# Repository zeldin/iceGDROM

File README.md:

iceGDROM
========

This is an implementation of IDE and the "Sega Packet Interface"
as used by the Dreamcast GD-ROM drive, using an iCE40 FPGA.

In addition to the IDE interface itself, and the accompanying CD-DA
interface, the FPGA bitstream implements an RV32EMC-compatible CPU and
an SD Card interface.  Software running on the CPU responds to
disc access commands from the Dreamcast by fetching data from disc
images on an SD Card.

For more detailed information, please see [the webpage][1].

This is free software (and hardware) licensed under the GNU
General Public License version 3.

Hardware
--------

The hardware is based on the Lattice iCE40-HX8K Breakout Board.
In order to connect this board to the Dreamcast motherboard, a
custom "riser board" with the appropriate connectors and some
additional components is used.  The design files for this can be
found in the `pcb/riser` directory.  The bill of materials can be
found in the file `pcb/riser/bom.txt`.  The pin headers with a `J`
designation should be soldered to the Breakout Board (pins facing downwards).

The components CN4, R8, D1, and JP2 through JP4 are optional.  They
are a passthrough for a slave hard drive, and not used by the GD-ROM
emulator.

For the hardware to be complete, the following additional things are
needed:

* A USB-mini cable to connect CN6 to the Breakout Board.  This is how
  the Breakout Board is powered when not attached to a host computer.
* An SD Card module, to connect to CN5.
* Rubber feet or similar to support the weight of the board in the
  corners not resting on CN1.

Required tools
--------------

To build the FPGA bitstream, the following tools are needed:

* Yosys 0.6
* arachne-pnr
* icestorm

To build the RISC-V software, the following tools are needed:

* riscv32-unknown-elf gcc 10.2.0
* riscv32-unknown-elf binutils 2.34.0

Building
--------

Building is done by running GNU make.  Running make at the top level
will build everything, running it in a subdir will build that part.
Note that building in fpga requires the rv32 stuff to be built first.

The file `rv32/source/config.h` can be modified to adapt to the polarity
of the CD signal on the chosen SD Card module, or to enable debug traces
on the serial port of the FTDI chip.

In order to flash the FPGA bitstream to the breakout board, run
`make flash`.

Making image files
------------------

Building the project will also create a host tool in `tools/obj/makegdimg`
which can create image files from either `.gdi` files (for GD-ROM images)
or from `.nrg` or `.cdi` files (for MIL-CD and audio CD images).  The
image files should be named `DISC0000.GI0`, `DISC0001.GI0` etc on the
SD Card.  To switch between images, extract and reinsert the SD Card.

Acknowledgements
----------------

* RISC-V softcore "VexRiscv" was developed by Charles Papon
* GD-ROM connector pinout was provided by OzOnE
* SD Card and FAT code based on sdfatlib by Bill Greiman
* DiscJuggler reader code based on CDIrip by DeXT/Lawrence Williams

[1]: http://mc.pp.se/dc/gdromemu.html

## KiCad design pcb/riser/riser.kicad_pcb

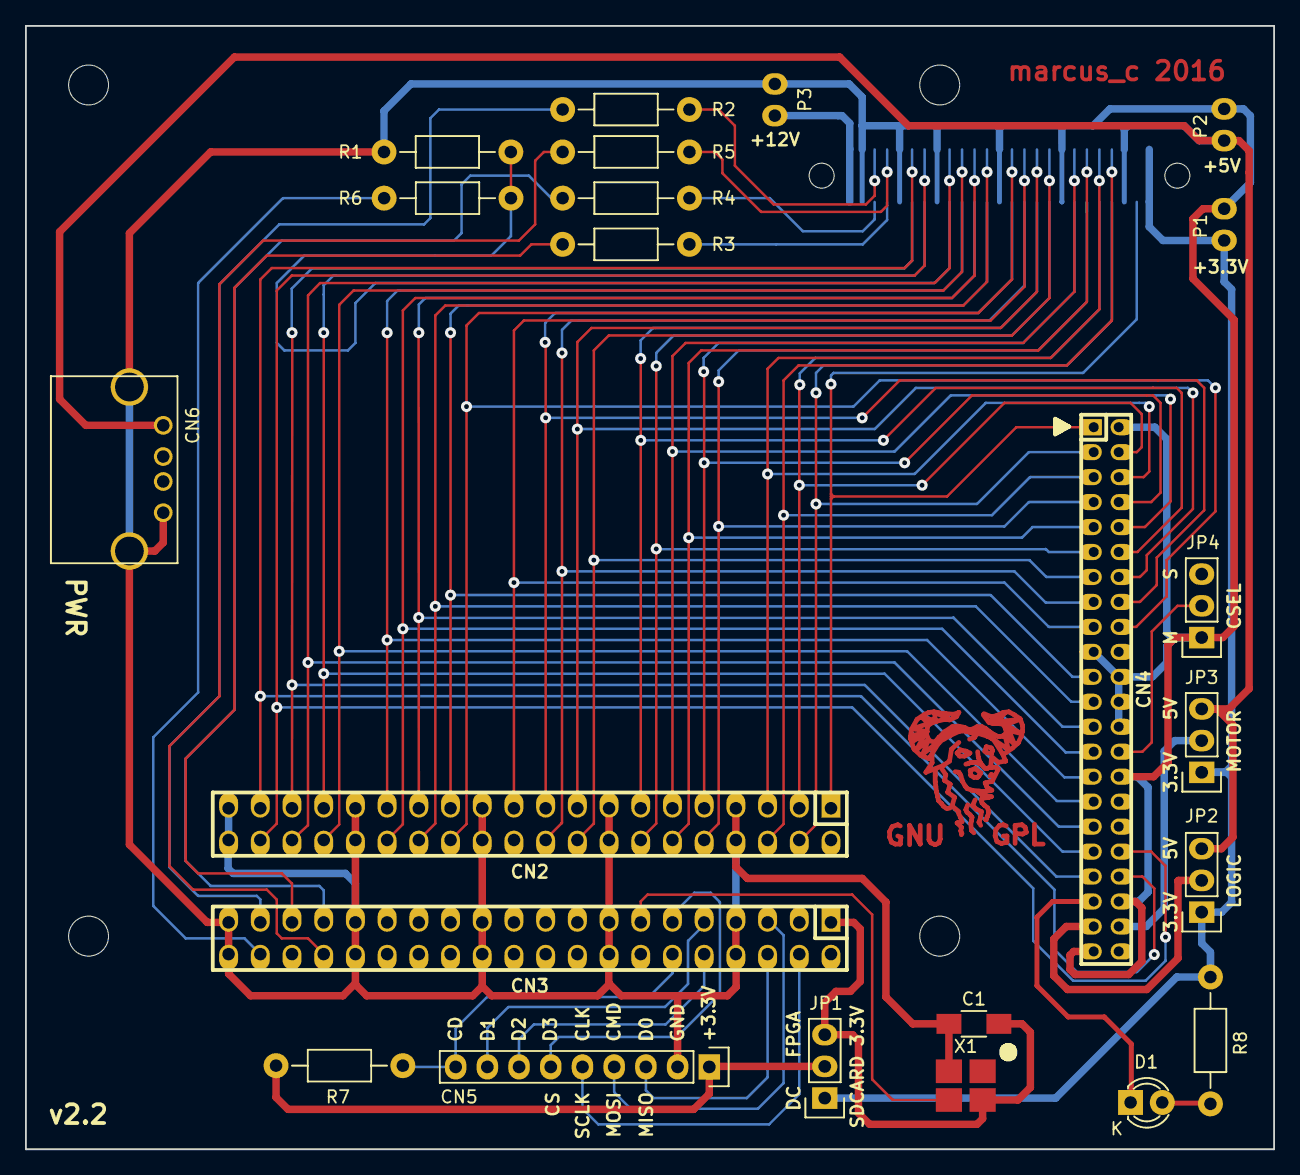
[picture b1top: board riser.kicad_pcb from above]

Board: 2 copper layers, 100.0 x 90.0 mm, 24 parts (1 on the bottom side), 57 nets.

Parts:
C1: 0.01u; C_1206_HandSoldering
CN1: Molex_52602_0579
CN2, CN3: CONN_02X20; pin_socket_20x2
CN4: CONN_02X22; pin_strip_2mm_22x2
CN5: CONN_01X09; Pin_Header_Straight_1x09
CN6: USB-A; USB_A
D1: LED; LED-3MM
JP1, JP2, JP3, JP4: JUMPER3; Pin_Header_Straight_1x03
P1, P2, P3: CONN_01X02; WireConnection_1.00mmDrill
R1, R7: 10k; Resistor_Horizontal_RM10mm
R2, R3, R4, R5, R6: 100; Resistor_Horizontal_RM10mm
R8: 1k; Resistor_Horizontal_RM10mm
X1: 11.2896M; SG-210STF

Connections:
+3V3: CN1.A1, CN1.B1, JP1.1, JP2.1, JP3.1, P1.1, R8.1
+3V3_FPGA: C1.1, CN3.1, JP1.3, X1.4
+5V: CN1.A3, CN1.B3, CN6.1, JP2.3, JP3.3, P2.1
+12V: CN1.A25, CN1.B25, P3.1
/A0: CN1.A19, CN2.33, CN4.35
/A1: CN1.B17, CN2.36, CN4.33
/A2: CN1.B19, CN2.38, CN4.36
/ACTIVEn: CN4.39, D1.1
/CCK: CN3.37, R2.1
/CD_CLK: CN1.B23, R2.2
/CS0n: CN1.A20, CN2.35, CN4.37
/CS1n: CN1.B20, CN2.37, CN4.38
/CSEL: CN4.28, JP4.2
/D0: CN1.B11, CN2.21, CN4.17
/D1: CN1.A11, CN2.20, CN4.15
/D2: CN1.B9, CN2.18, CN4.13
/D3: CN1.A9, CN2.14, CN4.11
/D4: CN1.B6, CN2.12, CN4.9
/D5: CN1.A6, CN2.10, CN4.7
/D6: CN1.B4, CN2.6, CN4.5
/D7: CN1.A4, CN2.4, CN4.3
/D8: CN1.A5, CN2.3, CN4.4
/D9: CN1.B5, CN2.5, CN4.6
/D10: CN1.A7, CN2.9, CN4.8
/D11: CN1.B7, CN2.11, CN4.10
/D12: CN1.A10, CN2.13, CN4.12
/D13: CN1.B10, CN2.17, CN4.14
/D14: CN1.A12, CN2.19, CN4.16
/D15: CN1.B12, CN2.26, CN4.18
/DMACKn: CN1.A16, CN2.29, CN4.29
/DMARQ: CN1.A14, CN2.25, CN4.21
/EBCK: CN3.35, R3.1
/ELRCK: CN3.34, R5.1
/EMPH: CN1.A17, R1.1, R6.2
/ESD: CN3.33, R4.1
/G_RST: CN1.A2, CN2.1, CN4.1
/INTRQ: CN1.B16, CN2.34, CN4.31
/IORDY: CN1.B15, CN2.30, CN4.27
/LRCK: CN1.B22, R5.2
/PB0: CN3.38, R6.1
/PB1: CN3.4, CN5.5
/PB2: CN3.5, CN5.4
/PB3: CN3.6, CN5.3
/PB4: CN3.9, CN5.8
/PB5: CN3.10, CN5.7
/PB6: CN3.11, CN5.6
/PB7: CN3.12, CN5.9, R7.1
/RDn: CN1.A15, CN2.27, CN4.25
/REFCLK: CN3.13, X1.3
/SCK: CN1.A22, R3.2
/SDAT: CN1.A23, R4.2
/VLOGIC: CN4.41, JP2.2
/VMOTOR: CN4.42, JP3.2
/WRn: CN1.B14, CN2.28, CN4.23
GND: C1.2, CN1.A8, CN1.A13, CN1.A18, CN1.A21, CN1.A24, CN1.B8, CN1.B13, CN1.B18, CN1.B21, CN1.B24, CN2.7, CN2.8, CN2.15, CN2.16, CN2.23, CN2.24, CN2.31, CN2.32, CN2.39, CN2.40, CN3.7, CN3.8, CN3.15, CN3.16, CN3.23, CN3.24, CN3.31, CN3.32, CN3.39, CN3.40, CN4.2, CN4.19, CN4.22, CN4.24, CN4.26, CN4.30, CN4.40, CN4.43, CN5.2, CN6.4, CN6.5, JP4.1, P1.2, P2.2, P3.2, R1.2, X1.2
unnamed: CN5.1, JP1.2, R7.2
unnamed: D1.2, R8.2

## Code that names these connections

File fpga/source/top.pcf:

set_io LED0 B5
set_io LED1 B4
set_io LED2 A2
set_io LED3 A1
set_io LED4 C5
set_io LED5 C4
set_io LED6 B3
set_io LED7 C3
set_io RXD B10
set_io TXD B12
# For use with breakout board, connect 11.2896MHz oscillator to L3
# set_io clk J3
set_io clk L3
set_io PORTB0 B2
set_io PORTB1 R1
set_io PORTB2 P1
set_io PORTB3 P2
set_io PORTB4 N3
set_io PORTB5 N2
set_io PORTB6 M2
set_io PORTB7 M1
set_io CDCLK  B1
set_io SCK    C1
set_io SDAT   D1
set_io LRCK   D2

set_io G_RST  R16
set_io D8     T15
set_io D7     T16
set_io D9     T13
set_io D6     T14
set_io D10    N12
set_io D5     P13
set_io D11    N10
set_io D4     M11
set_io D12    T11
set_io D3     P10
set_io D13    T10
set_io D2     R10
set_io D14    P8
set_io D1     P9
set_io D15    T8
set_io D0     T9
set_io DMARQ  T7
set_io WRn    R6
set_io RDn    T6
set_io IORDY  R5
set_io DMACKn T5
set_io INTRQ  R4
set_io CS0n   R2
set_io CS1n   T1
set_io A0     R3
set_io A1     T3
set_io A2     T2

set_frequency clkout 79.0272
set_frequency clkout_cpu 39.5136

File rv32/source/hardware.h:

#define SD_CD_PIN PINB
#define SD_CD_BIT PIN7

#define EMPH_BIT PIN0

#ifdef __ASSEMBLER__
#define _MMIO_BYTE(addr) addr
#define _MMIO_WORD(addr) addr
#else
#define _MMIO_BYTE(addr) (*(volatile uint8_t *)(void *)(addr))
#define _MMIO_WORD(addr) (*(volatile uint32_t *)(void *)(addr))
#endif

#define PORTA          _MMIO_BYTE(0xffffff00)
#define PINA           _MMIO_BYTE(0xffffff04)
#define DDRA           _MMIO_BYTE(0xffffff08)
#define PORTB          _MMIO_BYTE(0xffffff10)
#define PINB           _MMIO_BYTE(0xffffff14)
#define DDRB           _MMIO_BYTE(0xffffff18)
#define UDR0           _MMIO_WORD(0xffffff20)
#define UCSR0          _MMIO_WORD(0xffffff24)
#define UBRR0          _MMIO_WORD(0xffffff28)
#define TCNT0          _MMIO_WORD(0xffffff30)
#define OCR0           _MMIO_WORD(0xffffff34)
#define TIFR           _MMIO_WORD(0xffffff38)
#define TIMSK          _MMIO_WORD(0xffffff3c)

#define PIN0           0
#define PIN1           1
#define PIN2           2
#define PIN3           3
#define PIN4           4
#define PIN5           5
#define PIN6           6
#define PIN7	       7

#define PB0         PIN0
#define PB1         PIN1
#define PB2         PIN2
#define PB3         PIN3
#define PB4         PIN4
#define PB5         PIN5
#define PB6         PIN6
#define PB7         PIN7

#define RXC            7
#define TXC            6
#define UDRE           5
#define FE             4
#define DOR            3

#define OCIE0          0
#define OCF0           0

#define IDE_STATUS     _MMIO_BYTE(0xfffef000)
#define IDE_ERROR      _MMIO_BYTE(0xfffef004)
#define IDE_IOCONTROL  _MMIO_BYTE(0xfffef008)
#define IDE_IOPOSITION _MMIO_BYTE(0xfffef00c)
#define IDE_ALT_STATUS _MMIO_BYTE(0xfffef010)
#define IDE_IOTARGET   _MMIO_BYTE(0xfffef014)
#define IDE_DEVCON     _MMIO_BYTE(0xfffef018)
#define IDE_FEATURES   _MMIO_BYTE(0xfffef024)
#define IDE_SECCNT     _MMIO_BYTE(0xfffef028)
#define IDE_SECNR      _MMIO_BYTE(0xfffef02c)
#define IDE_CYLLO      _MMIO_BYTE(0xfffef030)
#define IDE_CYLHI      _MMIO_BYTE(0xfffef034)
#define IDE_DRVHEAD    _MMIO_BYTE(0xfffef038)
#define IDE_COMMAND    _MMIO_BYTE(0xfffef03c)

#define IDE_DATA_BUFFER  ((uint8_t *)0xfffef400)

#define SDCARD_CONTROL _MMIO_BYTE(0xfffee400)
#define SDCARD_DATA    _MMIO_BYTE(0xfffee404)
#define SDCARD_DIVIDER _MMIO_BYTE(0xfffee408)
#define SDCARD_CRC16   _MMIO_WORD(0xfffee410)
#define SDCARD_CRC7    _MMIO_BYTE(0xfffee414)

#define CDDA_CONTROL   _MMIO_BYTE(0xfffee800)
#define CDDA_READPOS   _MMIO_BYTE(0xfffee804)
#define CDDA_LIMIT     _MMIO_BYTE(0xfffee808)
#define CDDA_SCRATCHPAD _MMIO_BYTE(0xfffee80c)

#define CDDA_DATA_BUFFER ((uint8_t *)0xfffeec00)

#ifdef __ASSEMBLER__
#define _BV(bit) (1<<(bit))
#else
#define _BV(bit) (1U<<(bit))
#endif

#define bit_is_clear(reg, bit) (!((reg) & _BV(bit)))
#define bit_is_set(reg, bit) (!bit_is_clear(reg, bit))
#define loop_until_bit_is_clear(reg, bit) do { } while(!bit_is_clear(reg, bit))
#define loop_until_bit_is_set(reg, bit) do { } while(!bit_is_set(reg, bit))

#define cli() asm volatile("csrrci zero,mstatus,8" ::: "memory")
#define sei() asm volatile("csrrsi zero,mstatus,8" ::: "memory")

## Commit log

2015-11-07 Imported from https://github.com/freecores/avr_core/blob/master/avr_core_v14.tar.gz (commit de4a72e841fa4453c0d7462c3643003bcae52689)
2015-12-09 Fix stuff that gives compilation errors on Yosys
2015-12-09 Fix DDR access in PPORT
2015-12-09 Add stuff to build for iCE40 8k
2015-12-09 Add PM programming through serial port
2015-12-09 Prevent ripple on TXD
2015-12-10 Put tech mappings in subdir, and add them to libdirs
2015-12-16 Double the clock speed
2016-01-08 Create a makefile for building the FPGA bitstream
2016-01-08 Build AVR PM data from source
2016-01-09 Add a make target from ihex upload using AVR109
2016-01-09 Use symbolic register addresses
2016-01-09 Correct USART control registers to match datasheet for ATmega64
2016-01-09 Assign SPI and PORTB to external pins
2016-01-09 AVR main code in C
2016-01-10 Add some debug macros
2016-01-10 Track dependencies
2016-01-10 Add hex debug macro
2016-01-10 Init SD card when inserted
2016-01-11 Fix fosc/2 mode for SPI
2016-01-11 Fix pmem hexdumps with repeating patterns
2016-01-17 Use 11.2896MHz oscillator instead of 12MHz
2016-02-02 Assign SPI as alternate functions on PORTB, like on ATmega32u4
2016-02-02 Fix delay loop for ms, and add one for cycles
2016-02-02 Separate SDcard I/O into a separate file, plus various fixes
2016-02-02 Enable SDcard and check for SDHC
2016-02-05 Fix two floating inputs to AVR core
2016-02-05 Add a timebase
2016-02-05 Fix prototype for debug_init()
2016-02-05 Create proper timeouts for sdcard init
2016-02-05 Lower SPI speed for more reliable operation
2016-02-06 Add function to read a block from the sdcard
2016-02-06 Increase size of data and program memory
2016-02-06 Mount FAT volume
2016-02-06 Read the root directory
2016-02-19 Add verilog for IDE interface
2016-02-20 Add a buffer for PIO data I/O
2016-02-20 Add an event when a certain number of data words have been transfered
2016-02-21 Set the HRST bit on hard reset
2016-02-21 Set BSY on hard reset and on data transfer complete
2016-02-21 Allow INTRQ to be negated from software
2016-02-21 Generate an AVR IRQ when an IDE event is fired
2016-02-22 Add a bit in iocontrol to enable PIO data transfers
2016-02-27 Remove superfluous checks in read/write_cycle
2016-02-28 Run IDE interface at twice the CPU clock speed
2016-02-28 Add code to process IDE commands
2016-02-28 Fix mapping of sdcard detect which was wrong after PORTB redesign
2016-03-01 Copy packet to a union for simplified access
2016-03-01 Move data access functionality to main thread of execution
2016-03-01 Increased size of program memory
2016-03-01 Replace hardcoded MIL-CD TOC with M'Boot
2016-03-20 Implemented DMA
2016-03-21 Fix bug that DM was written during IDE accesses
2016-04-02 Make COMMAND register controlled by IDE bus regardless of BSY state
    The AVR never writes to this register anyway, and the interface needs
    to be able to react to DMA command aborts.
2016-05-29 New clock configuration
    AVR core runs at oscillator*1.5 (17 MHz).
    IDE interface runs at 4x CPU speed (68 MHz).
2016-05-29 Removed link flag not supported by upstreams GCC
2016-05-29 Implement DMA read (hardcoded cluster mapping for now)
2016-05-29 Support PIO read as well
2016-05-30 Lookup file start cluster in directory
2016-06-03 Add an imagefile layer
2016-06-03 Get TOC and session data from image file
2016-06-05 Handle discs larger than 128M
2016-06-10 Implemented digital audio output
2016-06-10 Implement CD_PLAY and CD_SEEK commands
2016-06-12 Move SPI_CS to PB6, and reverse polarity of SD_CD
2016-07-03 Add design files for breakout board riser
2016-07-03 Update pin mapping for new design
2016-07-03 Tweak mounting hole positions
2016-07-14 Unmap PORTB0 as SPI slave select in (it's now used for EMPH)
2016-07-14 Final pin mapping update
2016-07-15 Get disk type from image file
2016-07-15 AVR always writes SECNR, regardless of BSY
2016-07-15 Increment image filename when extracting and reinserting the sdcard
2016-07-15 Add some missing includes
2016-07-15 Remove volatile flag on memory mapped BRAMs
2016-07-15 Silence IDE debug unless explicitly enabled
2016-07-15 Swap byteorder of CD-DA to match Dreamcast internal format
2016-07-18 Handle other sector formats than 2048 (WIP)
2016-07-19 Use 2352 byte sector format for all tracks
2016-07-22 New SPI implementation for higher transfer rates
2016-07-22 Create a DMA channel from SDCARD to IDE buffer
2016-07-22 Fix timer interrupt for new CPU clock
2016-07-23 Use SDCARD DMA also for CDDA data
2016-07-23 Add CRC16 calculation to SDCARD interface
2016-07-23 Reset CDDA and SDCARD blocks when AVR is reset
2016-07-24 Retry if sdcard read fails
2016-07-24 Generalize block cache handling to plain LRU
2016-07-24 Remove pointless debug trace
2016-07-24 Implement "any type" data read
2016-07-26 Implement CDDA repeat and subcode Q emulation
2016-07-26 Handle FAD/MSF specifications
2016-07-26 Increase size of DM
2016-07-26 Cache TOCs in RAM and use them to get CDDA track # and EMPH flag
2016-07-26 Use second TOC for HD-area CDDA
2016-07-26 Increase number of cache slots to use new larger DM
2016-07-27 Include TOC number flag in image region header
2016-07-27 Use LEDs to indicate SDCARD activity, and which image is selected
2016-07-29 Add a tool to create image files
2016-07-29 Add support for Nero5 files to image tool
2016-07-29 Add missing schematic library
2016-07-29 Fix broken standard components
2016-07-29 Make CD polarity configurable
2016-07-30 Add missing include
2016-07-30 Control debugging options through config.h
2016-08-07 Add a BOM for the riser board
2016-08-07 Added GPL and a readme
2016-09-09 Add a benchmark program
2016-09-19 Add a config to disable subchannel Q
2016-09-23 Use icebram to avoid resynthesis when only changing AVR code
2016-09-24 Change memory mapping for larger IDE aperture
2016-09-24 Add an extra IDE buffer and preload blocks into it
2016-09-24 Avoid wasting 2 BRAMs in IDE buffer...
2016-09-24 Improve reliability of imgfile_need_to_read
2016-12-20 makegdimg: Add Nero track type 0x0200
2016-12-21 makegdimg: Handle pre-Nero5 images
2016-12-26 Update README.md
    Fix typo in filename pattern for disk images
2016-12-29 makegdimg: Handle DiscJuggler images
2017-03-29 clkgen: Fix typo
2017-07-02 Decrease via drill size to get a larger annular ring
2017-07-07 Add a DMA transfer test program
2018-03-29 Change capacitor value in BOM to a range
    Any value in this range is fine according to the SPXO datasheet.
2018-12-02 Add cdrdao support to makegdimg (for single session discs)
2019-07-03 Updating the schematic file to include the new style of referencing kicad components with some minor aesthetic changes. Also updating orientation of the LED in the PCB.
2020-07-07 Use nextpnr-ice40 for place and route
2020-07-07 Fix off-by-one on some seeks
2020-07-08 Add PIO mode to data transfer test program
2020-07-08 Fix multiple read glitch in PIO mode
2020-07-08 Improve performance of forwards seeks
2020-07-09 Fix scanning of lone slashes in cdrdao
2020-07-09 AVR109: Fix flash addressing
2020-07-09 Update upload make target for newer avrdude
2020-07-09 AVR109: Flush TX on attaching
2020-07-10 Keep intermediary build products for tests
2020-07-10 Remove obsolete processing of BRAM hex files
2020-07-11 Add a CDDA test program
2020-07-11 Update SECNR on CDDA playback end
2020-07-11 Ignore footprint info cache
2020-07-11 makegdimg: Handle subchannel data on swapped audio tracks
2020-07-11 v2.2
2020-08-08 Replace AVR core with RISC-V
2020-08-08 Allow 32-bit access to IDE and CDDA block rams
2020-08-09 Fix cycle counts in delay loops
2020-08-09 Extend BRR to 16 bits
2020-08-09 Use memory lookahead to allow the CPU frequency to be doubled
2020-09-12 Replace picorv32 with VexRiscv
2020-09-12 Boost CPU frequency to 39.5 MHz
2020-09-12 Remove no longer needed AVR RTL
2020-09-13 Correct SDCARD speeds
2020-09-13 Move rodata before text for lower addresses
2020-09-13 Update README to reflect change of softcore ISA
2020-09-13 Fix bad sdcard indicator
2020-09-13 Strip any debug sections
2020-09-13 Move more data into imm12 range
2020-09-13 Minor optimizations
2020-09-13 SDCARD CRC improvements
2020-09-13 Add a skipahead index for accelerated seek
2022-06-14 Enable zicsr extension when compiling RISC-V code
2023-02-18 Fix include of the wrong header
2023-02-18 Workaround for yosys > 0.17 failing to infer BRAM
